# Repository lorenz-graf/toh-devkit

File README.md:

# TOH DevKit

Breadboard dev cover for The Other Half (TOH) connector of the Jolla Phone 2026.

> [!WARNING]
> **Work in progress, not tested yet.** Neither the PCBs nor the printed parts (STLs) have been built or tried on a phone. The designs are based on Jolla's models, the official spec and measurements, but expect mistakes. Use at your own risk, and check fit and voltages with a multimeter before putting anything on your phone.

A 3D-printed back cover ("The Other Half", TOH) for the Jolla Phone 2026 (`jp2601`) that brings the phone's 7 TOH contacts out to a mini breadboard on the back of the phone, for prototyping covers with a microcontroller (RP2040-Zero) and plug-in modules (IR, sub-GHz, LoRa, RFID, …).

**Status (2026-11):** cover model and both boards designed, boards ordered. Not yet printed or assembled, so nothing here is tested on hardware yet. Firmware (RP2040 I²C target) and the phone-side package are still to be written.

TOH spec (pins, ID resistors, memory chip format): https://docs.sailfishos.org/Develop/Hardware/JP2601-TOH/. Phone-side daemon: [symbiosis](https://github.com/sailfishos/symbiosis).

## Overview

```
 phone spring pins
        │
 [contact board]  in the cover's indent, gold pads toward the phone   (pcb/contact/)
        │  6 thin wires through a 9 × 3 mm slot in the cover
 [breakout board] on a mini breadboard stuck to the outside of the cover   (pcb/breakout/)
        │  6-pin header: 5V GND SDA SCL INT ID
 [RP2040-Zero + modules] on the breadboard
```

- **Cover** (`model/`): the community **cTOH-M** frame from Jolla's [toh-designs](https://github.com/sailfishos/toh-designs) repo, laid flat for printing, plus the wire slot. The frame already has an indent for a contact board; nothing else was changed
- **Contact board:** 0.6 mm thick, meant to sit flush in the indent. 7 gold pads should touch the phone's pins; vias carry the signals to wire pads on the other side, right above the slot
- **Breakout board:** takes the wires, sets the cover's ID, ties INT to GND, protects the phone from USB backfeed, and gives the breadboard a clean 6-pin header

## The phone's TOH connector (from the spec)

7 spring pins on the phone (lower right of the back, 2.90 mm pitch, rows of 4 and 3). The cover only needs flat pads.

| Pin | Signal | What it does | Rules |
|---|---|---|---|
| 1 | VIN | power *into* the phone (5–9 V, max 1 A; charges it) | **never connect on this cover** |
| 2 | GND | ground | |
| 3 | ID | resistor to GND tells the phone what kind of cover this is | never tie to 3.3 V/5 V |
| 4 | INT | pulled up to 1.8 V by the phone; the cover pulls it low = "attached" | never drive high |
| 5 | SCL | I²C clock, 3.3 V, 400 kHz | the phone has the pull-ups: none on the cover |
| 6 | SDA | I²C data, 3.3 V | same |
| 7 | 5V OUT | the cover's only power supply, 5 V, max 1 A, switched by the phone | |

What happens on attach, as I understand the spec and symbiosis (not verified on hardware yet): INT goes low → the phone switches 5 V on → reads the ID resistor through an ADC → with 6.2 kΩ (development ID) it uses vendor/product `0000/0000` and keeps 5 V on; with 10 kΩ it waits 100 ms and reads a memory chip at I²C 0x50. INT going high again counts as "cover removed".

## Contact board ([pcb/contact/](pcb/contact/))

- 2 layers, **0.6 mm**, **ENIG** (gold; tin or OSP would oxidise under the spring pins). 27.1 × 10.45 mm, L-shaped = the cTOH-M indent minus 0.2 mm on every side
- **Phone side:** 7 round pads, 2.3 mm (same size as on Jolla's Inari Blue cover), at the pin positions. **Pin 1 is the square pad.** Nothing else on this side but traces under solder mask and covered vias, so it stays flat
- **Cover side:** 7 square wire pads over the slot, labelled; readable from outside through the slot:
  ```
  top row:     5V   SCL   ID   VIN
  bottom row:    GND   INT   SDA
  ```
- **Power lines** (VIN, GND, 5V) are 0.5 mm wide with 1.2 mm wire pads: on paper about 1 A with only a few degrees of warming (calculated, not tested). The board is meant for every cover project, including battery covers that charge the phone through VIN. Signals are 0.2 mm
- **On this dev cover leave the VIN pad unconnected**

## Breakout board ([pcb/breakout/](pcb/breakout/))

Most options are **solder jumpers**: small pads next to each other on the board. "Bridged" ones are joined by a thin copper link: to open one, cut that link with a sharp knife and check with a multimeter that it's really open. To close a jumper, put a blob of solder across the pads (remove it with solder wick to open it again). All jumpers come in the state you need to get started, so you only touch them for a specific feature.

1.6 mm, HASL, 31 × 23.6 mm. Top row: 6 holes for the wires from the cover (`5V GND SDA SCL INT ID`, no VIN on purpose). Bottom row: 6-pin header into the breadboard, same order.

**Through-hole or SMD (v3):** D1, R1 and R2 each have SMD pads between their through-hole pads, wired in parallel. Fit **either** the through-hole part **or** the SMD part, whichever you have: an SMA Schottky diode (e.g. SS14, cathode band toward the header like the through-hole one) and 1206 resistors (0805 should fit too when hand-soldering). The SMD pads only show without the through-hole parts: [renders/breakout-bare.png](renders/breakout-bare.png). v3 is designed but not made yet; the boards I ordered are v2 (through-hole only, [Gerbers](pcb/breakout/dev-toh-breakout-v2-gerbers-ordered.zip)).

| Part | Does | As shipped / fitted | Change it when |
|---|---|---|---|
| **D1** 1N5817 (Schottky), or SS14 (SMA) on the SMD pads | sits in the phone's 5 V line. I *think* it's needed: many small boards (the RP2040-Zero included) tie their 5 V pin directly to USB VBUS, and I couldn't find out whether the phone protects its 5 V output (pin 7) against power coming back in. With D1, USB should be able to stay plugged in while the cover is on the phone (flashing, serial debug). Costs ~0.3–0.45 V, so the breadboard gets ~4.6 V instead of 5 V; fine for the microcontroller, which makes its own 3.3 V | fitted, band (K) toward the header | keep it unless you know pin 7 is protected |
| **R1** 6.2 kΩ (THT or 1206) | ID resistor for **DEV mode** (development ID, no memory chip; the phone should detect the cover without any firmware). **Use while developing** | fitted | |
| **R2** 10 kΩ (THT or 1206) | ID resistor for **CHIP mode** (the microcontroller pretends to be the memory chip; see [ID-modes.md](ID-modes.md)). Only once that firmware works reliably | fitted | |
| **JP2** DEV / CHIP (3-pad solder jumper, top right) | connects ID to R1 or R2 | **DEV** (left + middle bridged) | to CHIP: cut the left bridge, check with a multimeter, bridge middle + right with solder. **Never bridge all three** (≈ 3.8 kΩ, not a valid ID: I expect the phone not to recognise it and switch 5 V off) |
| **JP1** INT-GND (solder jumper) | ties INT to GND, so the phone sees the cover as attached | **bridged** | only if the MCU should drive INT itself later (as far as I understand, symbiosis doesn't support cover interrupts yet; its README lists proper interrupt handling as missing). Then cut it and drive INT open-drain (pull low, never high) |
| **JP4** (solder jumper under "5V MEAS") + **J3** (2-pin header) | J3 is a measuring point in the 5 V line; JP4 bridges it so 5 V works without anything on J3 | JP4 **bridged**, J3 empty | to measure what the RP2040 and modules draw (limit 1 A): cut JP4 once, put a multimeter (current range) across J3. **From then on J3 needs a jumper cap or Dupont wire** for normal use, or re-bridge JP4 with solder |
| **JP3** "NO USB" (solder jumper next to D1) | bridges D1, so modules get the full 5 V instead of ~4.6 V (e.g. the RDM630 RFID reader is specified for 4.75–5.25 V) | **open** | bridge only while the microcontroller is **not** on USB (bridged, nothing stops USB power from flowing back into the phone); open it again before plugging USB in |

Header out (`J2`, left to right): `5V` (after D1) · `GND` · `SDA` · `SCL` · `INT` · `ID`.

## ID modes in short

| | DEV | CHIP |
|---|---|---|
| ID resistor (JP2) | 6.2 kΩ | 10 kΩ |
| Phone sees | vendor/product `0000/0000`, no name | whatever the RP2040's emulated memory chip says (planned `0000/0001`, name, product link) |
| Firmware needed for detection (expected, not tested) | no | **yes** (answer at 0x50 within 100 ms, payload with `PO` = true, otherwise I expect the phone to switch 5 V off again) |
| Use for | developing, flashing, anything unstable | the real-product path, the "install the companion app" link |

Firmware should always serve both 0x50 and its own address (planned 0x42); then switching modes is only the jumper. Details, checks and failure symptoms: **[ID-modes.md](ID-modes.md)**.

## Parts

- Printed: [model/ctohm-dev.stl](model/ctohm-dev.stl) (frame) + [model/ctohm-bump.stl](model/ctohm-bump.stl) (camera bump)
- Contact board: order with 0.6 mm, ENIG, vias tented (Gerbers: [pcb/contact/dev-toh-contact-gerbers.zip](pcb/contact/dev-toh-contact-gerbers.zip))
- Breakout board: order with defaults, 1.6 mm, HASL ([pcb/breakout/dev-toh-breakout-gerbers.zip](pcb/breakout/dev-toh-breakout-gerbers.zip))
- For the breakout: 1N5817 (or SS14, SMA), 6.2 kΩ and 10 kΩ (1/4 W THT, or 1206/0805 SMD), 1×6 and 1×2 male header, jumper cap or female–female Dupont wire (only after cutting JP4)
- 6 thin wires (28 AWG silicone works), 170-hole mini breadboard (self-adhesive, fits on the back), RP2040-Zero, CA glue or thin double-sided tape for the contact board, multimeter

## Printing

- **Frame:** load as exported, outside face down. cTOH-M's authors recommend ASA with X/Y scaled to 100.3 % (needs an enclosed printer); PETG should work without. PLA is not advised (softens from the phone's heat, creeps under the clip tension). Check the side hooks for overhangs in the slicer
- **Bump:** open side down, roof up. Its built-in supports stand under the roof (extended down to the bed in this export, they used to start 0.16 mm above it)
- The indent floor sits at 0.8 mm and the inner surface at 1.4 mm, both multiples of 0.2 mm, so 0.2 mm layers give the 0.6 mm pocket depth exactly
- **After printing check:** the cover clips on firmly, the bump fits its opening, the indent is clean (no support remains) and ~0.6 mm deep. If the board is tight in the indent, sand its edge lightly

## Assembly

1. **Contact board** into the indent, gold pads toward the phone, square pad 1 next to the slot side. Glue it at the edges. It must sit flush; if pins don't make contact later, shim it from behind (a layer of tape)
2. **Breakout:** D1 (band toward the header), R1 6.2 kΩ, R2 10 kΩ (through-hole or SMD, one per position), 6-pin header (pins down). Leave the jumpers as shipped (DEV, INT-GND bridged, JP4 bridged, NO USB open)
3. **Wires:** six wires (not VIN) from the contact board's wire pads, out through the slot, into the breakout's top holes by label. Keep them short and flat; stick the breadboard on the outside of the cover near the slot
4. **RP2040-Zero** on the breadboard: header `5V` → Zero `5V`, `GND` → `GND`, `SDA`/`SCL` → an I²C pair (e.g. GP0 = SDA, GP1 = SCL), optionally `INT`/`ID` to spare pins for monitoring only. No I²C pull-ups. 3.3 V modules: the Zero's 3V3 is weak, give radios their own 3.3 V regulator from `5V`

## First test (planned; no firmware needed)

Once it's built: cover on the phone, then over SSH (developer mode, no root):

```
cat /sys/class/yft_pogo_pin/*adc_value      # DEV: 600–799, CHIP: 800–999, nothing attached: ~1820
cat /sys/class/yft_pogo_pin/*int_state      # 0 = attached
cat /sys/class/yft_pogo_pin/*5v_out_state   # 1 = 5 V on (must stay 1)
gdbus call --system --dest org.sailfishos.tohd1 --object-path /org/sailfishos/tohd1 \
  --method org.freedesktop.DBus.ObjectManager.GetManagedObjects   # DEV: VendorId 0, ProductId 0
```

Then you should measure ~4.6 V between the header's `5V` and `GND`.

## If something goes wrong: check first

- **Contact trouble** (not detected, flaky I²C, wrong ADC value) or the cover lifting/rattling at the bottom: the cTOH-M frame holds only with 12 hooks on the two long sides, while Jolla's covers have two more clips right next to the contact pads (`renders/clips-compare.png`). The 7 springs may push the plate away from the pins. Test: press the cover down over the pads; if it then works, that's it. Quick fix: shim the contact board. Real fix: add those two clips or a stiffening rib in `scripts/make_dev_cover.py`

- **Breadboard gets no 5 V:** JP4 was cut for measuring and J3 has no jumper (or re-bridge JP4). Also check the cover is detected (`5v_out_state` = 1)
- **ADC reads ~400–600 / 5 V switches off right away:** all three JP2 pads bridged
- **CHIP mode doesn't work:** [ID-modes.md](ID-modes.md) → "If CHIP mode doesn't work". First go back to DEV to separate firmware problems from contact problems

## Phone side (to do)

- Accessing the TOH I²C bus needs root or a program allowed by a config file: symbiosis reads `*.yaml` from `/usr/share/tohd-1/tohs/<vid>/<pid>/` (DEV: `0000/0000/`, CHIP: `0000/0001/`). Planned config (one RPM installs it into both): `access: i2c-dev` for the polling program, `devices:` listing 0x42 and 0x50 (every address used must be listed), and a `user-unit` that starts the polling service on attach and stops it on detach. Format: symbiosis `doc/configuration.md`
- The program then borrows the bus over D-Bus (`org.sailfishos.tohd1`, `BorrowI2cDevAccess`) and polls the RP2040 (e.g. every 100–200 ms: status register first, data only when something is new)
- As far as I found, Sailfish has no way to prompt for a companion app on attach; in CHIP mode the product link at least ends up on D-Bus (`ProductWebsite`) for a helper to show

## Next steps

- Print, assemble, first test as above
- RP2040 firmware: I²C target at 0x42 (register protocol with an "enter bootloader" command reserved), later the memory-chip image at 0x50
- Phone package (RPM): config + polling service as above
- Modules: IR first, then CC1101 (433 MHz), RDM630 (125 kHz RFID; 5 V UART, needs a divider to 3.3 V), SX1262 LoRa (own 3.3 V regulator)

## Design notes (why it is like this)

- **No pogo pins, no screw:** the phone has the springs; Jolla's own covers use a small flat pad board held by the cover. Here it sits in the cTOH-M frame's indent
- **Positions:** taken from Jolla's cover model and the pin positions in the official back drawing, then checked by hand with a cheap caliper against my phone and my Inari Blue cover: pin tips ~0.9 mm, sticking out ~0.5 mm; the Inari's pads ~2.3 mm at 2.90 mm pitch, flush with its inner surface. Measured from the two clips next to the connector, the model and my Inari seemed to agree within ~0.15 mm (`renders/measure-cover-pads.png`). Honestly, I YOLO'd it: these are my own measurements and might be off; the first print and the real boards will show

- **0.6 mm board in a 0.6 mm indent** should give flush pads, as I measured on my Inari; the springs should then see about the same height as with Jolla's covers
- **Wires out the back through a slot** under the board's arm, so the solder blobs sit in the slot instead of lifting the board
- **Polling instead of INT:** as far as I understand, symbiosis only uses INT for attach/detach today
- **1N5817 kept** even though it costs ~0.4 V: I couldn't find out whether the phone protects pin 7, and the RP2040-Zero has no diode of its own. If someone knows pin 7 is protected, it could go

### Coordinates used in the scripts

`u` = mm from the phone's right edge, `v` = mm from its bottom edge, seen from behind. Pins: 1 (19.8, 8.45), 2 (19.8, 5.55), 3 (16.9, 8.45), 4 (16.9, 5.55), 5 (14.0, 8.45), 6 (14.0, 5.55), 7 (11.1, 8.45). Model frame (`model/`): X = −37 + u, Y = −78.8 + v, inside of the cover = +Z. KiCad top view = seen from behind the phone: X = 100 − u, Y = 100 − v.

## Files

- `model/ctohm-dev.step|stl`: cover frame (outside face down, ready for the slicer). `model/ctohm-bump.stl`: camera bump. `model/indent-outline.txt`: indent outline used for the PCB
- [pcb/contact/](pcb/contact/), [pcb/breakout/](pcb/breakout/): `make_board.py` generates the KiCad board (edit the script, not the board), `README.md` with details, `dev-toh-*-gerbers.zip` = current design (breakout: v3; the ordered v2 is `dev-toh-breakout-v2-gerbers-ordered.zip`)
- [ID-modes.md](ID-modes.md): DEV vs CHIP mode in detail
- `renders/`: `dev-cover.png` (model + slot), `pcb-check.png` (contact board in the cover), `breakout.png` (with through-hole parts), `breakout-bare.png` (bare board, shows the SMD pads), `clips-compare.png` (Jolla's clips vs cTOH-M's), `measure-cover-pads.png` (measurements on a real Inari Blue)
- `scripts/`: FreeCAD/Blender/Python scripts for the models and images

## Rebuilding

Tools: FreeCAD (`freecadcmd`), Blender, KiCad 10 (`kicad-cli`, Python `pcbnew`), Python 3 with Pillow.

- **Models:** clone [sailfishos/toh-designs](https://github.com/sailfishos/toh-designs), then from `scripts/`: `TOH_DESIGNS=/path/to/toh-designs freecadcmd -c "exec(open('make_dev_cover.py').read())"` (and `make_bump.py`)
- **Contact board:** needs the footprint `Jolla_JP2601_TOH_Contact_7P_P2.90mm_Pads` (`JOLLATOH_LIB=/path/to/JollaTOH.pretty python3 make_board.py`); the generated `.kicad_pcb` already embeds it, so opening and ordering need nothing extra. **Breakout:** `python3 make_board.py` (KiCad standard libraries only)
- **Check and export:** `kicad-cli pcb drc --severity-all -o drc.rpt <board>.kicad_pcb` (0 errors), then the Gerber/drill commands in each board's README
- **Images:** usage line at the top of each script

## License and credits

BSD-3-Clause, see [LICENSE](LICENSE): use, modify and redistribute freely (also commercially), keep the copyright notice, and don't use the authors' names to promote derived products.

- `model/` files are derived from Jolla's [toh-designs](https://github.com/sailfishos/toh-designs) (the cTOH-M community frame and camera bump, and measurements from `jolla/toh-3d-model.step`), © 2026 Jolla Mobile Ltd, also BSD-3-Clause. Thanks to the cTOH-M authors. Not affiliated with or endorsed by Jolla
- Everything else (PCBs, scripts, docs, renders): © 2026 Lorenz Graf and contributors

Contributions (pull requests) are accepted under the same BSD-3-Clause license.

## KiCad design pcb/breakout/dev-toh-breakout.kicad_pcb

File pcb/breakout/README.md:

# Breakout board for the dev cover (v3)

Sits on the breadboard. The 6 wires from the contact board ([../contact/](../contact/), via the cover's wire slot) are soldered into the top row of holes; a 6-pin 2.54 mm male header on the bottom row plugs into the breadboard. Render: `../../renders/breakout.png`.

| Header pin | Signal | Note |
|---|---|---|
| 5V | phone 5 V after D1 | feeds the RP2040-Zero's 5V pin (live out of the box via JP4) |
| GND | GND | |
| SDA, SCL | I²C | no pull-ups (the phone has them) |
| INT | INT | tied to GND by JP1 (= "cover attached"). Cut JP1's bridge if the MCU should drive INT later |
| ID | ID | to GND through R1 6.2 kΩ (DEV mode) or R2 10 kΩ (CHIP mode), chosen by JP2; see below and [ID-modes.md](../../ID-modes.md) |

- **v3: through-hole or SMD.** D1, R1, R2 each have SMD pads (D1S: SMA, R1S/R2S: 1206) centred between their through-hole pads, in parallel (same nets). Fit one of the two per position, not both. D1S's cathode (pad 1) points toward the header like D1's; the silkscreen band between D1S and D1's cathode hole marks it for both. The SMD footprints have no courtyard (the overlap with the THT part is intended) and no silkscreen of their own. Bare render: `../../renders/breakout-bare.png`. v2 (THT only) is what was ordered: `dev-toh-breakout-v2-gerbers-ordered.zip`
- D1 1N5817 (Schottky) in the 5 V line: anode = phone side (top), cathode band (K) = header side. Stops the RP2040's USB 5 V from flowing back into the phone
- **ID mode selector JP2** (3-pad solder jumper at the top right, labelled DEV / CHIP): both resistors are fitted permanently; JP2 connects ID to one of them.
  - **DEV** (factory default, left + middle pad bridged): R1 **6.2 kΩ** = dev ID, works without firmware. Develop here
  - **CHIP**: cut the DEV bridge (knife between left and middle pad, check with the multimeter that ID–R1 is open), then bridge middle + right pad with solder: R2 **10 kΩ** = memory-chip mode, needs RP2040 firmware answering at 0x50 with `PO` = true
  - Back to DEV: remove the CHIP blob (solder wick), bridge left + middle again
  - Never bridge all three (that's 6.2 k ∥ 10 k ≈ 3.8 kΩ: unreserved value, the phone switches 5 V off)
- **5V MEAS** (bottom left): J3 (2-pin header) with **JP4** (solder jumper, **bridged** at the factory) in parallel. As shipped, 5 V just works through JP4; J3 can stay empty. **To measure** what the RP2040 and modules draw (limit 1 A): cut JP4 once (knife between the pads, check with the multimeter that it's open), then put the multimeter (current range) across J3. **From then on J3 must be bridged** (jumper cap or female–female Dupont wire) for normal use, or JP4 re-bridged with solder
- **JP3 "NO USB"** (2-pad solder jumper next to D1, **open** by default): bridges D1, so the modules get the full 5 V instead of ~4.6 V (e.g. the RDM630 wants 4.75–5.25 V). **Only while the RP2040 is NOT on USB**: bridged, nothing stops USB 5 V from flowing back into the phone. Open it again (solder wick) before plugging USB back in
- VIN (pin 1) is deliberately not brought out
- Parts: D1 1N5817 (diode kit) or SS14 (SMA), R1 6.2 kΩ + R2 10 kΩ (KUBOWAI kit; or 1206/0805), 1×6 + 1×2 male header (spare strip from an RP2040-Zero pack), jumper cap or a female–female Dupont wire for J3 (only needed after JP4 is cut)
- Wire holes: 1.0 mm, for the 28 AWG silicone wire (strip, push through, solder)

## Files

- `make_board.py` generates `dev-toh-breakout.kicad_pcb` + `.kicad_pro`; edit the script, not the board. DRC: `kicad-cli pcb drc --severity-all -o drc.rpt dev-toh-breakout.kicad_pcb` (0 errors)
- `dev-toh-breakout-gerbers.zip`: current design (v3), for an order. `dev-toh-breakout-v2-gerbers-ordered.zip`: what was ordered 2026-11-07 (same export commands as [../contact/README.md](../contact/README.md))

## Ordering (JLCPCB)

Separate item in the same order as the contact board: 2 layers, **1.6 mm**, HASL (lead-free) is fine, 5 pcs.

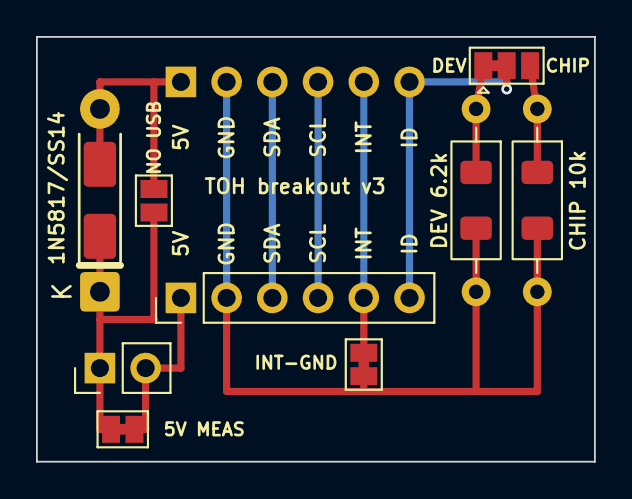
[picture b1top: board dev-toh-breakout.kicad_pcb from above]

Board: 2 copper layers, 31.0 x 23.6 mm, 13 parts (0 on the bottom side), 10 nets.

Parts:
D1: D_DO-41_SOD81_P10.16mm_Horizontal
D1S: D_SMA
J1, J2: PinHeader_1x06_P2.54mm_Vertical
J3: PinHeader_1x02_P2.54mm_Vertical
JP1, JP4: SolderJumper-2_P1.3mm_Bridged_Pad1.0x1.5mm
JP2: SolderJumper-3_P1.3mm_Bridged12_Pad1.0x1.5mm
JP3: SolderJumper-2_P1.3mm_Open_Pad1.0x1.5mm
R1, R2: R_Axial_DIN0207_L6.3mm_D2.5mm_P10.16mm_Horizontal
R1S, R2S: R_1206_3216Metric_Pad1.30x1.75mm_HandSolder

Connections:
5V: J2.1, J3.2, JP4.2
5V_D: D1.1, D1S.1, J3.1, JP3.2, JP4.1
5V_PHONE: D1.2, D1S.2, J1.1, JP3.1
GND: J1.2, J2.2, JP1.2, R1.2, R1S.2, R2.2, R2S.2
ID: J1.6, J2.6, JP2.2
ID_A: JP2.1, R1.1, R1S.1
ID_B: JP2.3, R2.1, R2S.1
INT: J1.5, J2.5, JP1.1
SCL: J1.4, J2.4
SDA: J1.3, J2.3
